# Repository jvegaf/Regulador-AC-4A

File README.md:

# Regulador AC 4A

El Circuito esta basado en el regulador de 3800W que hizo Jose Manuel (@TerrazoCultor) que puedes ver en su blog 

https://100ciaencasa.blogspot.com.es/2014/02/circuitos-utiles-02-regulador-corriente.html

Este regulador puede controlar hasta una corriente de 900W, ideal para un taladro o un torno manual.

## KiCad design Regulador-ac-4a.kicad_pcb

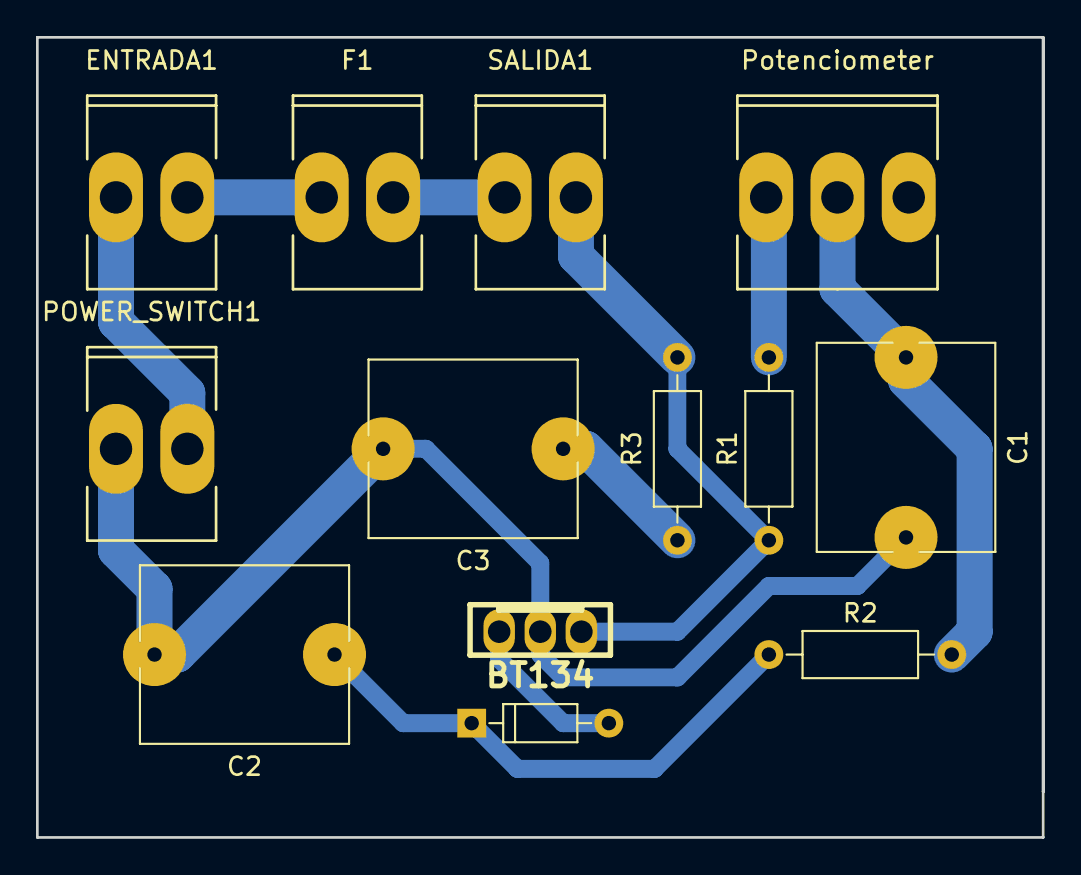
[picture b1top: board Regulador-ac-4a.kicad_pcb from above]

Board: 2 copper layers, 55.9 x 44.5 mm, 12 parts (0 on the bottom side), 9 nets.

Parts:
BT134: sot82_std
C1, C2, C3: 100 nf 400V; C_Rect_L11.5mm_W9.8mm_P10.00mm_MKT
ENTRADA1: Socket_MOLEX-KK-RM3-96mm_Lock_2pin_straight
F1: Fuse; Socket_MOLEX-KK-RM3-96mm_Lock_2pin_straight
POWER_SWITCH1: Socket_MOLEX-KK-RM3-96mm_Lock_2pin_straight
Potenciometer: 220K; Socket_MOLEX-KK-RM3-96mm_Lock_3pin_straight
R1: 3K3; R_Axial_DIN0207_L6.3mm_D2.5mm_P10.16mm_Horizontal
R2: 8K2; R_Axial_DIN0207_L6.3mm_D2.5mm_P10.16mm_Horizontal
R3: 47 OHM; R_Axial_DIN0207_L6.3mm_D2.5mm_P10.16mm_Horizontal
SALIDA1: Socket_MOLEX-KK-RM3-96mm_Lock_2pin_straight

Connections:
unnamed: BT134.1, R1.1, R3.1, SALIDA1.2
unnamed: BT134.2, C1.2, C2.2, C3.2, POWER_SWITCH1.1
unnamed: C1.1, Potenciometer.2, R2.2
unnamed: C2.1, R2.1
unnamed: C3.1, R3.2
unnamed: ENTRADA1.1, POWER_SWITCH1.2
unnamed: ENTRADA1.2, F1.1
unnamed: F1.2, SALIDA1.1
unnamed: Potenciometer.1, R1.2

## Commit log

2018-01-10 measures added
